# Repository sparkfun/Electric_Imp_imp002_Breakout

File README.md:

SparkFun Electric Imp imp002 Breakout
============================

[*Electric Imp imp002 Breakout (BOB-12958)*](https://www.sparkfun.com/products/12958)

The imp002 is a surface mount Electric Imp module with its own breakout board and more pins than the original imp001 card.

Repository Contents
-------------------
* **/Documentation** - SVG files of the board layout.
* **/Hardware** - Eagle PCB layout files
* **/Production** - Files to support SparkFun production

Documentation
--------------

* **[Hookup Guide](https://learn.sparkfun.com/tutorials/electric-imp-breakout-hookup-guide)** - Basic hookup guide

Product Versions
----------------

* [BOB-12958](https://www.sparkfun.com/products/12958)- Hardware version 1.0. 

Version History
---------------

License Information
-------------------

This product is _**open source**_! 

Please review the LICENSE.md file for license information. 

If you have any questions or concerns on licensing, please contact techsupport@sparkfun.com.

Distributed as-is; no warranty is given.

- Your friends at SparkFun.

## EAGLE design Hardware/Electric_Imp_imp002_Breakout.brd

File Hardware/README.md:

SparkFun Electric Imp imp002 Breakout Board Design Files
========================================================

The .sch and .brd files hare are Eagle CAD schematic and PCB design files from SparkFun Electronics.
A freeware version of Eagle can be found [here](http://www.cadsoftusa.com/download-eagle/freeware/). 

License
---------
This product is open source! 
The hardware is released under [Creative Commons ShareAlike 4.0 International](https://creativecommons.org/licenses/by-sa/4.0/).

Please use, reuse, and modify these files as you see fit. Please maintain attribution to SparkFun Electronics and release anything derivative under the same license.

Distributed as-is; no warranty is given.

- Your friends at SparkFun.

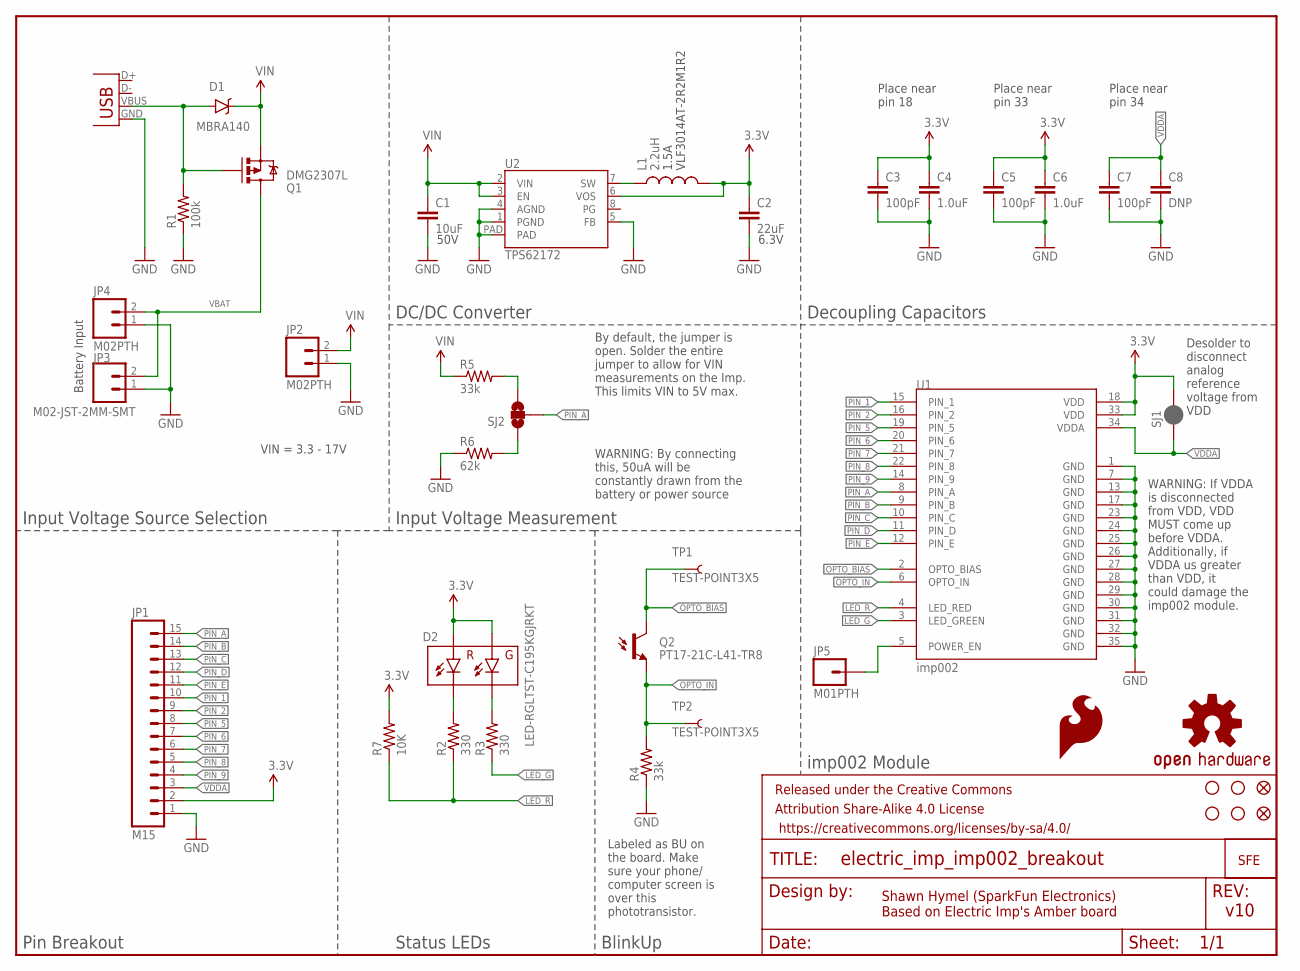
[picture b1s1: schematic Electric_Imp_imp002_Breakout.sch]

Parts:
C1: 10uF; 1210
C2: 22uF; 0805
C3, C5, C7: 100pF; 0603-CAP
C4, C6: 1.0uF; 0603-CAP
C8: DNP; 0603-CAP
D1: MBRA140; SMA-DIODE
D2: LED-RGLTST-C195KGJRKT; LTST-C195KGJRKT
FID1, FID2: FIDUCIAL1X2; FIDUCIAL-1X2
FRAME1: FRAME-LETTER; CREATIVE_COMMONS
JP1: M15; 1X15
JP2, JP4: M02PTH; 1X02
JP3: M02-JST-2MM-SMT; JST-2-SMD
JP5: M01PTH; 1X01
L1: 2.2uH; VLF4012A
LOGO1: OSHW-LOGOS; OSHW-LOGO-S
LOGO2: SFE_LOGO_FLAME.1_INCH; SFE_LOGO_FLAME_.1
Q1: DMG2307L; SOT23-3
Q2: PT17-21C-L41-TR8
R1: 100k; 0603-RES
R2, R3: 330; 0603-RES
R4, R5: 33k; 0603-RES
R6: 62k; 0603-RES
R7: 10K; 0603-RES
SJ1: JUMPER-PAD-2-NC_BY_PASTE; PAD-JUMPER-2-NC_BY_PASTE_YES_SILK
SJ2: JUMPER-PAD-3-NOFULL_BOX_SILK; PAD-JUMPER-3-NO_YES_SILK_FULL_BOX
STANDOFF1, STANDOFF2, STANDOFF3, STANDOFF4: STAND-OFF
TP1, TP2: TEST-POINT3X5; PAD.03X.05
U1: imp002; ELECTRIC_IMP_IMP002
U2: TPS62172; WSON-8-PAD
U$9: SFE_LOGO_NAME_WEB; SFE-NEW-WEBLOGO
X1: USBSMD; USB-MINIB

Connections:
3.3V: C2.1, C3.1, C4.1, C5.1, C6.1, D2.P$1 (GA), D2.P$2 (RA), JP1.2, L1.P$2 (2), R7.2, SJ1.2, U1.18 (VDD), U1.33 (VDD), U2.6 (VOS)
GND: C1.2, C2.2, C3.2, C4.2, C5.2, C6.2, C7.2, C8.2, JP1.1, JP2.1, JP3.1 (2), JP4.1, R1.1, R4.1, R6.1, U1.1 (GND), U1.7 (GND), U1.13 (GND), U1.17 (GND), U1.23 (GND), U1.24 (GND), U1.25 (GND), U1.26 (GND), U1.27 (GND), U1.28 (GND), U1.29 (GND), U1.30 (GND), U1.31 (GND), U1.32 (GND), U1.35 (GND), U2.1 (PGND), U2.4 (AGND), U2.5 (FB), U2.PAD, X1.GND
LED_G: R3.1, U1.3 (LED_GREEN)
LED_R: R2.1, R7.1, U1.4 (LED_RED)
unnamed: L1.P$1 (1), U2.7 (SW)
unnamed: D1.A, Q1.1 (G), R1.2, X1.VBUS
unnamed: D2.P$4 (RC), R2.2
unnamed: D2.P$3 (GC), R3.2
unnamed: R5.2, SJ2.3
unnamed: R6.2, SJ2.1
OPTO_BIAS: Q2.C, TP1.P$1, U1.2 (OPTO_BIAS)
OPTO_IN: Q2.E, R4.2, TP2.P$1, U1.6 (OPTO_IN)
PIN_1: JP1.10, U1.15 (PIN_1)
PIN_2: JP1.9, U1.16 (PIN_2)
PIN_5: JP1.8, U1.19 (PIN_5)
PIN_6: JP1.7, U1.20 (PIN_6)
PIN_7: JP1.6, U1.21 (PIN_7)
PIN_8: JP1.5, U1.22 (PIN_8)
PIN_9: JP1.4, U1.14 (PIN_9)
PIN_A: JP1.15, SJ2.2, U1.8 (PIN_A)
PIN_B: JP1.14, U1.9 (PIN_B)
PIN_C: JP1.13, U1.10 (PIN_C)
PIN_D: JP1.12, U1.11 (PIN_D)
PIN_E: JP1.11, U1.12 (PIN_E)
POWER_EN: JP5.1, U1.5 (POWER_EN)
VBAT: JP3.2 (1), JP4.2, Q1.3 (D)
VDDA: C7.1, C8.1, JP1.3, SJ1.1, U1.34 (VDDA)
VIN: C1.1, D1.C, JP2.2, Q1.2 (S), R5.1, U2.2 (VIN), U2.3 (EN)

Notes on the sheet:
50V
6.3V
1.5A
VLF3014AT-2R2M1R2
Place near pin 18
Place near pin 33
Place near pin 34
Desolder to disconnect analog reference voltage from VDD
Input Voltage Source Selection
Input Voltage Measurement
DC/DC Converter
Decoupling Capacitors
imp002 Module
Pin Breakout
Status LEDs
BlinkUp
By default, the jumper is open. Solder the entire jumper to allow for VIN measurements on the Imp. This limits VIN to 5V max.
Battery Input
Shawn Hymel (SparkFun Electronics) Based on Electric Imp's Amber board
v10
VIN = 3.3 - 17V
WARNING: By connecting this, 50uA will be constantly drawn from the battery or power source
WARNING: If VDDA is disconnected from VDD, VDD MUST come up before VDDA. Additionally, if VDDA us greater than VDD, it could damage the imp002 module.
Labeled as BU on the board. Make sure your phone/ computer screen is over this phototransistor.

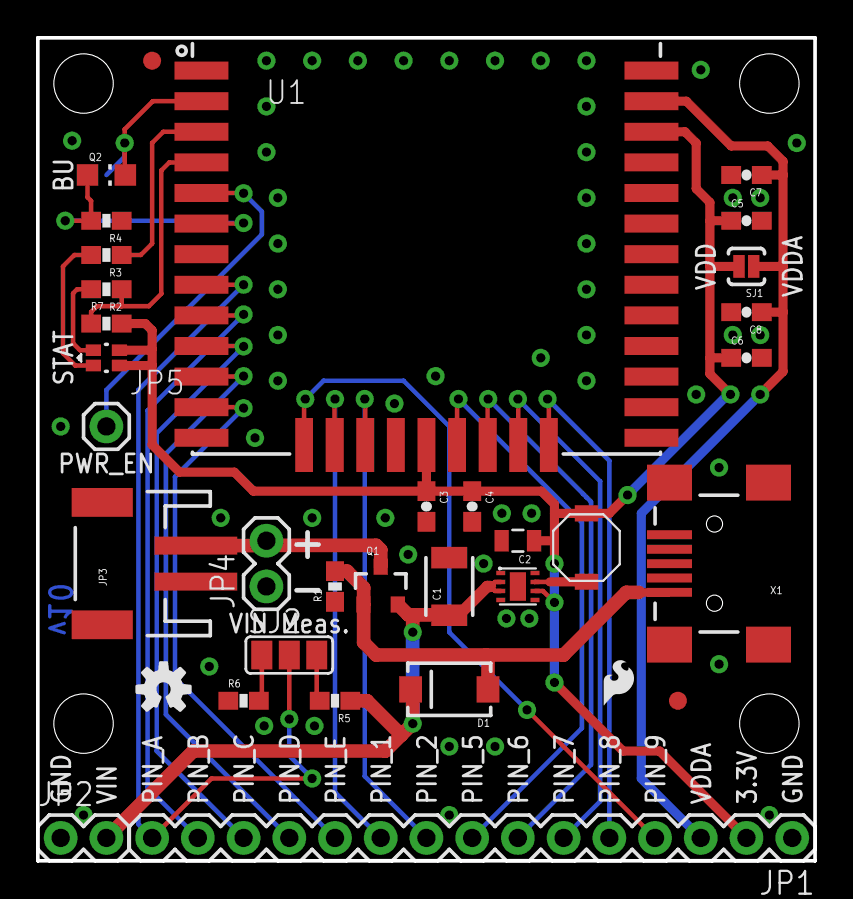
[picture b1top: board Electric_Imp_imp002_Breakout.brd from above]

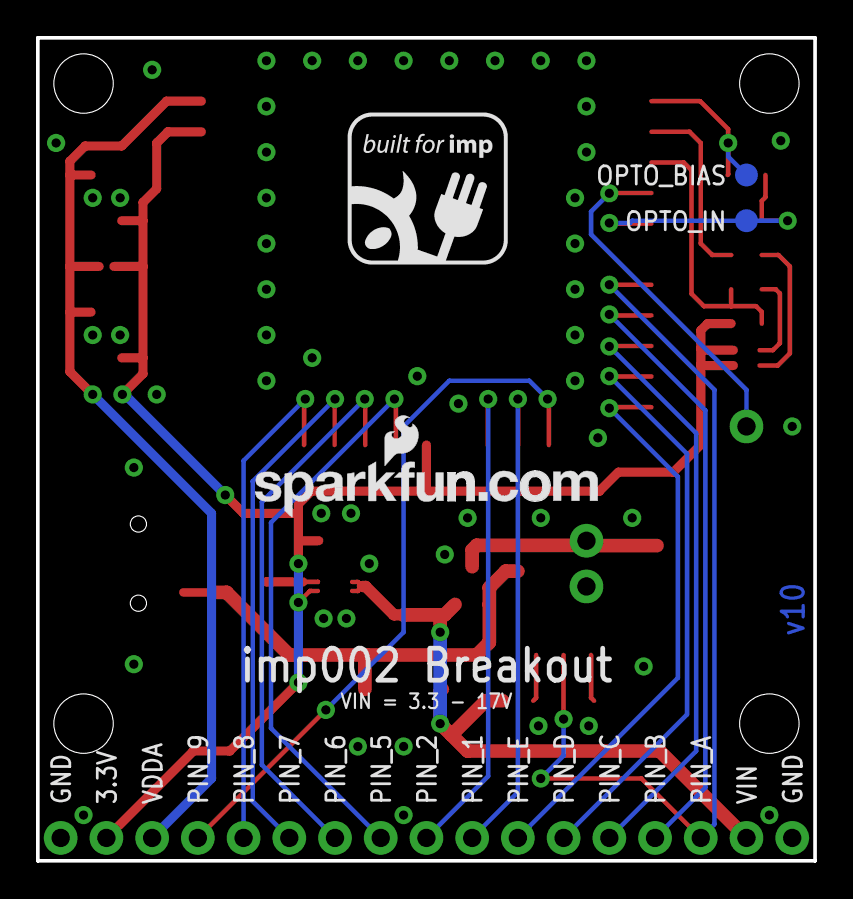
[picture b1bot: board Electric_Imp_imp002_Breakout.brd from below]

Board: 2 copper layers, 43.2 x 45.7 mm, 42 parts (3 on the bottom side), 28 nets.

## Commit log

2014-05-15 Created blank schematic and updated .gitignore
2014-05-19 Created initial schematic and part placement
2014-05-21 Added automatic voltage source selector and battery level monitor in schematic
2014-05-27 Finished v01 prototype for review
2014-05-27 Made changes from review. Fixed VIn sense divider. Updated packages to remove $ symbols. Added +/- silk to battery. Added voltage input range text on sch and brd. Moved decoup caps on bottom of imp t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
2014-05-27 Changed 68k resistor to 62k
2014-11-05 Added silk to the 3-way jumper, moved marking for dual-color diode to outside footprint, and changed phototransistor gain resistor to 33k
2014-11-05 Changed rev number to v10
2014-11-11 Added 10k pullup on LED_R line. Added warning notes to the solder jumpers.
2014-11-19 Fixed 3-way jumper name. Added PROD_ID to components lacking it. Added device name to phototransistor in schematic.
2014-11-19 Fixed issues from GitHub for reds.
2014-11-25 created panel v10
2015-06-22 Created PNG and PDF versions of the schematic.
2015-06-22 Fixed note about VDD/VDDA jumper in schematic.
2015-06-25 Added readme and license info.
2015-06-26 Cleaning up repo layout, fixing directory names, updating README, adding correct license file

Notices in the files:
parts and their libraries:
SparkFun-Aesthetics: Licensing: Creative Commons ShareAlike 4.0 International - https://creativecommons.org/licenses/by-sa/4.0
SparkFun-Aesthetics: Released under the Creative Commons Attribution Share-Alike 4.0 License
SparkFun-Aesthetics: Released under the Creative Commons
